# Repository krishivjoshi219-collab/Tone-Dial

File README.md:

# 💀🐚 TONE DIAL (SOUL KING BROOK EDITION) 🎻⚡
> *"YO-HO-HO-HO! I HAVE NO EARS BUT THIS SYNTH SOUNDS SO FIRE BROOO!!!"*

YO WHAT IS UP HACK CLUB REVIWRES AND RAMDOM GITHUB PEOPLE !!!!!!!!! 👋
so basically this is my project for **Half-Life Week 3 (Make Some Noise / Music week)** and its called **TONE DIAL** (yes from skypiea in one piece bcuz brook is litterly the GOAT no debate 😤). 

and like its NOT just a dumb boring speaker or some basic 3 button macropad that just beep boops lol... its a **LITTERAL STANDALONE SYNTHESIZER + OPTICAL THEREMIN + USB MIDI CONTROLLER + AI DESK PET COMPANION THINGY** THAT ACTUALLY LIVES ON MY DESK !!!!!!! (bruh it took so long to finilaze the idea my brain was melting)

---

## 📸 LOOK AT THIS BEAUTY !!!!!!!

| 3D Enclosure Exploded View (Onshape) | The Actual PCB (KiCad 3D Viewer) |
| :---: | :---: |
|  |  |

---

## 🤯 WHAT DOES THIS EVEN DO LIKE ACTUALLY?!?!?!

* 🎹 **CHORD SYNTH THAT DOESNT SOUND TRASH:** 4 mech switches wired to play a fire C-maj7 chord (C4, E4, G4, B4) runing on circuitpython `synthio` + `audiomixer` so it actually sounds like real music and not a microwave buzzer lmao
* 📡 **OPTICAL THEREMIN (PEW PEW LASER THINGY):** i put a literal VL53L0X laser sensor on it so i can just wave my hand in the air like a madman to bend pitch and filter cutoff without even touching anything like a crazy sci-fi theremin !!!!!!!
* 💀 **BROOK AI COMPANION (GROQ CLOUD GO BRRR):** if you click the rotary encoder knob it talks to Groq Llama 3.1 8B Instant over wifi to tell you unhinged skull jokes (*"Can I see your panties? Wait I don't have eyes! Yo-ho-ho-ho!"*)
* 🫀 **TAMAGOTCHI HEART ATTACK MELTDOWN:** brook has a "soul meter" on the round LCD. every 3 mins it drops 1%. if it hits 0%, HE GETS A LITTERAL HEART ATTACK and a super loud screech alarm blasts until you do **CPR by spamming Key 1 + Key 4 together** to revive him lol 😭
* 🎛️ **SLIDER & DIAL:** a 60mm slide potentiometer for sweeping the filter brightness + EC11 dial for volume !!
* 📺 **ROUND SCREEN:** 1.28 inch round GC9A01 LCD showing brooks animated skull face, his soul level, and the theremin laser distance in real time.

---

## 💻 THE HARDWARE (HOW I ALMOST BLEW UP MY PC LOL)

fun fact: i had to disgn this ENTIRE 3D enclosure on a litteral ancient 2012 intel 2nd gen Core i5 tower with NO gpu and onshape litterly froze my pc like 50 times at 3 AM and crashed my browser and i wanted to cry but WE FINIALLY MADE IT OUT ALIVE !!!!!!!! (i spent 40 mins wondering why my extrude was broken until i relized i had to click new instead of add lmaooo)

🔗 **ONSHAPE 3D MODEL LINK (INSPECT IT IN YOUR BROWSER):**  
👉 https://cad.onshape.com/documents/b2faf6ddaed43afc5f23715c/w/a55dc42bd27790c65e64b376/e/ee16a28059401b4fbaad3de5 (go check it out in 3D its actually sick !!)

* **Brain:** ESP32-S3-DevKitC-1 (N16R8) with dual core 240mhz + 8MB octal psram (core 0 does the wifi + groq ai and core 1 does audio so the synth never stutters or lags)
* **Audio Out:** MAX98357A I2S 3W class D amp going into a 40mm speaker inside a custom acoustic sealed chamber
* **Display:** 1.28" circular SPI TFT (GC9A01) 240x240
* **Sensor:** VL53L0X I2C laser distance sensor
* **Keys:** 4x mechanical keyswitches + 1x 60mm slide fader + EC11 encoder knob
* **Enclosure:** custom 12 degree tilted desktop wedge tray with built-in pcb holder clips and a nice clean USB C rectangle hole so you can plug it in without snapping the port !!

---

## 📂 WHAT IS WHERE IN THIS REPO (SO YOU DONT GET LOST)

```
├── assets/             <-- screenshots & 3d renders for the readme!
├── firmware/
│   ├── code.py         <-- the big brain non-blocking circuitpython code!
│   ├── brook.bmp       <-- 96x96 pixel art of brook with his afro & tiny hat
│   ├── brook.png       <-- preview pic so you can see how cool he looks
│   └── README.md       <-- how to flash it without crying
├── Tone Dial/
│   ├── Tone Dial.kicad_pcb  <-- full 2 layer pcb layout that took forever
│   ├── Tone Dial.kicad_sch  <-- the massive schemetic
│   ├── Tone Dial.kicad_pro  <-- kicad project file
│   └── Tone Dial.step       <-- 3d step model of the pcb
├── CAD/
│   ├── Tone Dial - Base Tray.stl <-- 3D printable bottom clamshell tray from Onshape
│   └── Tone Dial - Top.stl       <-- 3D printable top faceplate from Onshape
├── Gerbers/
│   ├── Tone Dial.zip        <-- ready to order gerbers for jlcpcb
│   └── Tone Dial-*.gbl/gtl/drl <-- loose production files
├── BOM.csv                  <-- bill of materials (kept under budget lets gooo)
└── JOURNAL.md               <-- my devlog for hack club reviewers!
```

---

## 🚀 HOW TO RUN THE FIRMWARE

1. plug in the esp32-s3 with a usb c cable
2. drop **CircuitPython 9.x** onto the board
3. open the `CIRCUITPY` drive on your pc
4. copy `code.py` and `brook.bmp` from `firmware/` right into the root of `CIRCUITPY`
5. put these libraries inside the `lib/` folder:
   - `adafruit_midi`
   - `adafruit_vl53l0x`
   - `adafruit_display_text`
   - `adafruit_requests`
   - `gc9a01`
6. (optional) add your wifi ssid and groq api key in `settings.toml` so brook can talk back to you!
7. JAM OUT AND DONT LET BROOK DIE OF A HEART ATTACK !!!!!!!!

---

### BIG SHOUTOUT TO HACK CLUB HALF LIFE REVIWRES PLEASE APPROVE MY GRANT SO I CAN SOLDER THIS BEAUTY IRL TYSM <33333333333

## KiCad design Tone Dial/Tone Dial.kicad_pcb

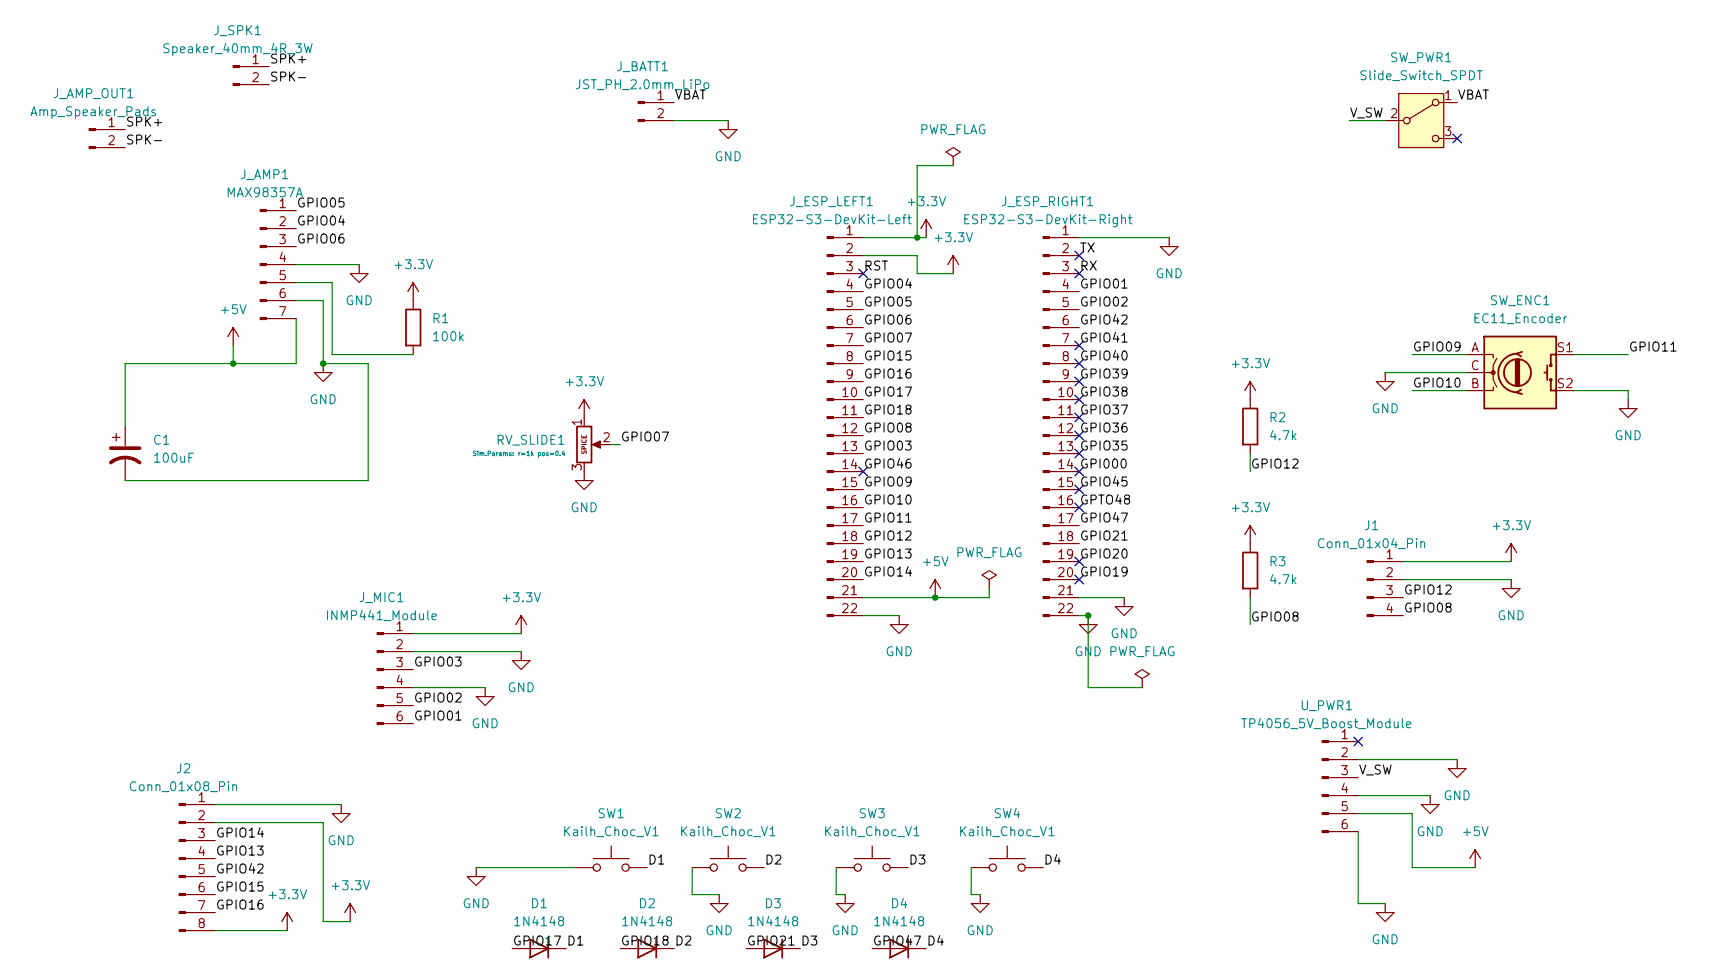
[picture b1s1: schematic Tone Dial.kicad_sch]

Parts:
C1: 100uF; CP_Radial_D6.3mm_P2.50mm
D1, D2, D3, D4: 1N4148; D_DO-35_SOD27_P7.62mm_Horizontal
J1: Conn_01x04_Pin; PinSocket_1x04_P2.54mm_Vertical
J2: Conn_01x08_Pin; PinSocket_1x08_P2.54mm_Vertical
J_AMP1: MAX98357A; PinHeader_1x07_P2.54mm_Vertical
J_AMP_OUT1: Amp_Speaker_Pads; PinHeader_1x02_P2.54mm_Vertical
J_BATT1: JST_PH_2.0mm_LiPo; JST_PH_B2B-PH-K_1x02_P2.00mm_Vertical
J_ESP_LEFT1: ESP32-S3-DevKit-Left; PinSocket_1x22_P2.54mm_Vertical
J_ESP_RIGHT1: ESP32-S3-DevKit-Right; PinSocket_1x22_P2.54mm_Vertical
J_MIC1: INMP441_Module; PinSocket_1x06_P2.54mm_Vertical
J_SPK1: Speaker_40mm_4R_3W; JST_PH_B2B-PH-K_1x02_P2.00mm_Vertical
R1: 100k; R_Axial_DIN0207_L6.3mm_D2.5mm_P7.62mm_Horizontal
R2, R3: 4.7k; R_Axial_DIN0207_L6.3mm_D2.5mm_P7.62mm_Horizontal
RV_SLIDE1: 10k_Slide_Pot; Potentiometer_Bourns_PTA6043_Single_Slide
SW1, SW2, SW3, SW4: Kailh_Choc_V1; SW_Cherry_MX_1.00u_PCB
SW_ENC1: EC11_Encoder; RotaryEncoder_Alps_EC11E-Switch_Vertical_H20mm
SW_PWR1: Slide_Switch_SPDT; SW_Slide_SPDT_Straight_CK_OS102011MS2Q
U_PWR1: TP4056_5V_Boost_Module; PinSocket_1x06_P2.54mm_Vertical

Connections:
+3.3V: J1.1, J2.2, J2.8, J_ESP_LEFT1.1, J_ESP_LEFT1.2, J_MIC1.1, R1.1, R2.1, R3.1, RV_SLIDE1.1
+5V: C1.1, J_AMP1.7, J_ESP_LEFT1.21, U_PWR1.5
/D1: D1.1 (K), SW1.2
/D2: D2.1 (K), SW2.2
/D3: D3.1 (K), SW3.2
/D4: D4.1 (K), SW4.2
/GPI000: J_ESP_RIGHT1.14
/GPIO01: J_ESP_RIGHT1.4, J_MIC1.6
/GPIO02: J_ESP_RIGHT1.5, J_MIC1.5
/GPIO03: J_ESP_LEFT1.13, J_MIC1.3
/GPIO04: J_AMP1.2, J_ESP_LEFT1.4
/GPIO05: J_AMP1.1, J_ESP_LEFT1.5
/GPIO06: J_AMP1.3, J_ESP_LEFT1.6
/GPIO07: J_ESP_LEFT1.7, RV_SLIDE1.2
/GPIO08: J1.4, J_ESP_LEFT1.12, R3.2
/GPIO09: J_ESP_LEFT1.15, SW_ENC1.A
/GPIO10: J_ESP_LEFT1.16, SW_ENC1.B
/GPIO11: J_ESP_LEFT1.17, SW_ENC1.S1
/GPIO12: J1.3, J_ESP_LEFT1.18, R2.2
/GPIO13: J2.4, J_ESP_LEFT1.19
/GPIO14: J2.3, J_ESP_LEFT1.20
/GPIO15: J2.6, J_ESP_LEFT1.8
/GPIO16: J2.7, J_ESP_LEFT1.9
/GPIO17: D1.2 (A), J_ESP_LEFT1.10
/GPIO18: D2.2 (A), J_ESP_LEFT1.11
/GPIO19: J_ESP_RIGHT1.20
/GPIO20: J_ESP_RIGHT1.19
/GPIO21: D3.2 (A), J_ESP_RIGHT1.18
/GPIO35: J_ESP_RIGHT1.13
/GPIO36: J_ESP_RIGHT1.12
/GPIO37: J_ESP_RIGHT1.11
/GPIO38: J_ESP_RIGHT1.10
/GPIO39: J_ESP_RIGHT1.9
/GPIO40: J_ESP_RIGHT1.8
/GPIO41: J_ESP_RIGHT1.7
/GPIO42: J2.5, J_ESP_RIGHT1.6
/GPIO45: J_ESP_RIGHT1.15
/GPIO46: J_ESP_LEFT1.14
/GPIO47: D4.2 (A), J_ESP_RIGHT1.17
/GPTO48: J_ESP_RIGHT1.16
/RST: J_ESP_LEFT1.3
/RX: J_ESP_RIGHT1.3
/SPK+: J_AMP_OUT1.1, J_SPK1.1
/SPK-: J_AMP_OUT1.2, J_SPK1.2
/TX: J_ESP_RIGHT1.2
/VBAT: J_BATT1.1, SW_PWR1.1 (A)
/V_SW: SW_PWR1.2 (B), U_PWR1.3
GND: C1.2, J1.2, J2.1, J_AMP1.4, J_AMP1.6, J_BATT1.2, J_ESP_LEFT1.22, J_ESP_RIGHT1.1, J_ESP_RIGHT1.21, J_ESP_RIGHT1.22, J_MIC1.2, J_MIC1.4, RV_SLIDE1.3, SW1.1, SW2.1, SW3.1, SW4.1, SW_ENC1.C, SW_ENC1.S2, U_PWR1.2, U_PWR1.4, U_PWR1.6
unnamed: J_AMP1.5, R1.2

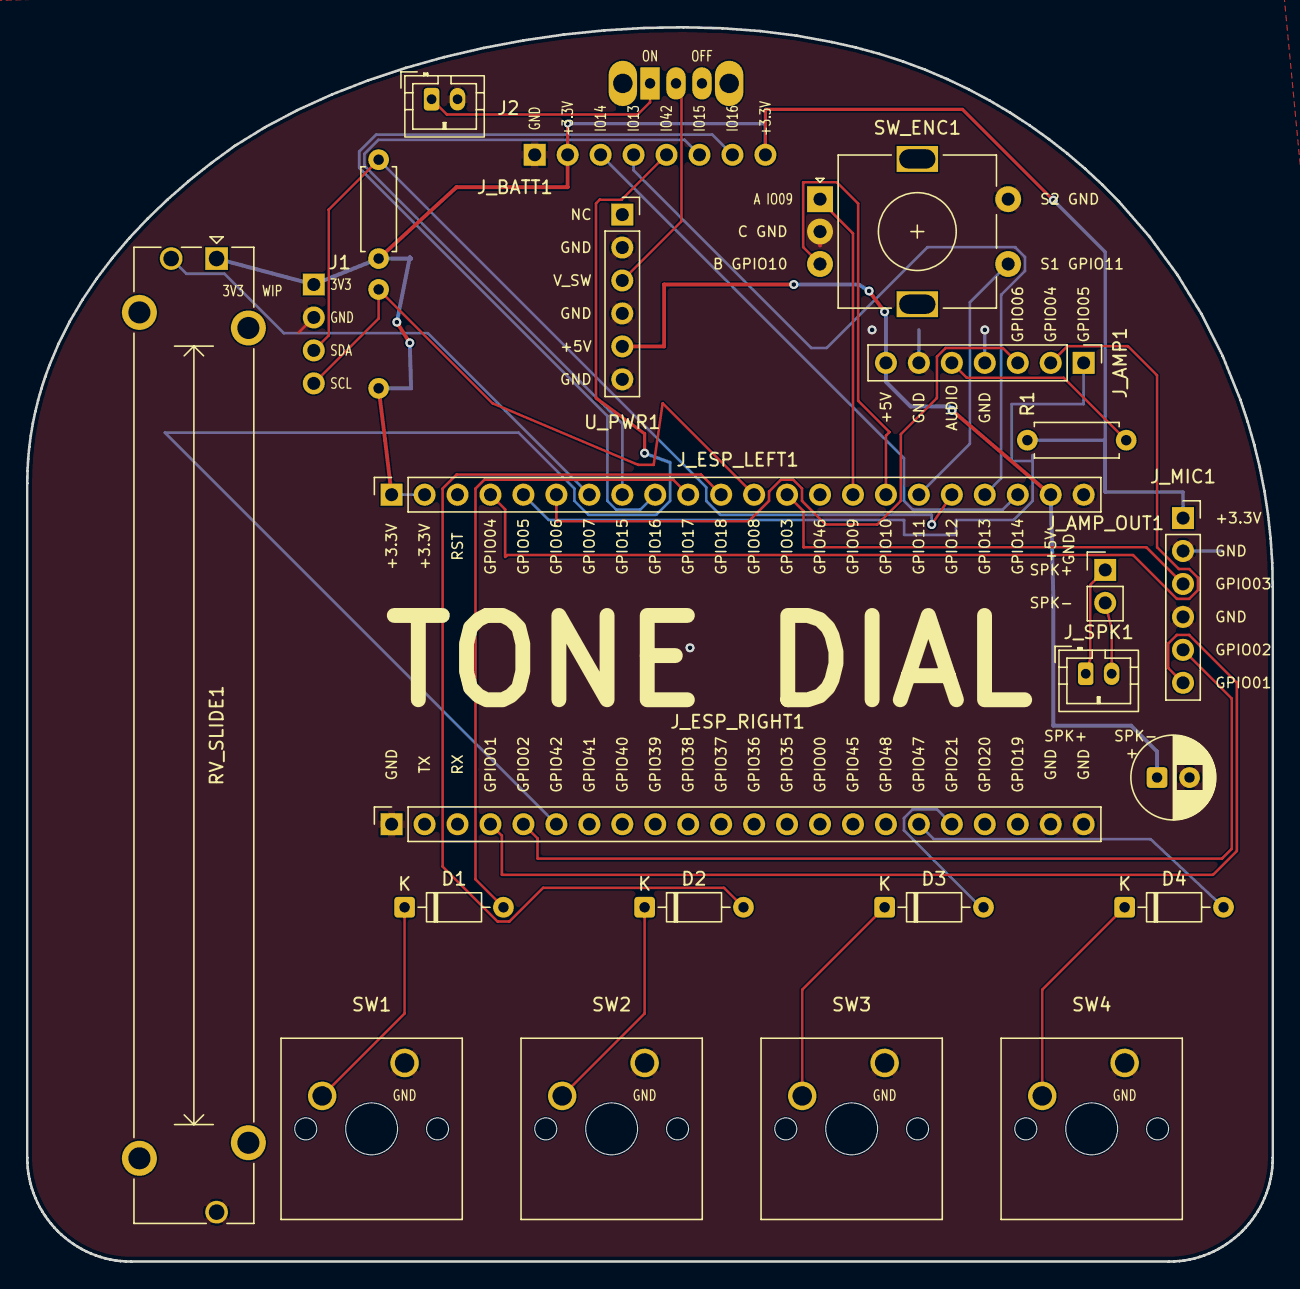
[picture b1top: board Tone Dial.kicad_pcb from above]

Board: 2 copper layers, 96.0 x 95.1 mm, 25 parts (0 on the bottom side), 33 nets.
